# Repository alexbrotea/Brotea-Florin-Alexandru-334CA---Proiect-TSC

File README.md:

## 1. Diagrama bloc

Mai jos este diagrama bloc a sistemului, ilustrand modul in care componentele interactioneaza cu unitatea centrala (MCU):

```mermaid
graph TD
    BATT[Baterie LiPo] -->|V_BATT| CHG[LiPo Charger MCP73831]
    USB[USB-C Connector] -->|5V| CHG
    CHG --> DCDC[DC/DC Converter]
    DCDC -->|3.3V| MCU(nRF52840 MCU)
    
    BATT -->|Monitorizare| FG[Fuel Gauge MAX17048]
    FG <-->|I2C| MCU
    
    MCU <-->|I2C| IMU[Senzor IMU BMI270]
    MCU <-->|I2C| HAP[Haptic Driver DRV2605L]
    
    MCU <-->|SPI| EPD_CON[E-Paper Display Connector]
    MCU -->|Control| EPD_DRV[E-Paper Drive Circuit]
    
    BTN[Butoane SW_UP, SW_ENT, SW_DN] -->|GPIO| MCU
    SWD[SWD Interface] <-->|Debug| MCU
```
## 2. Bill of Materials

| Componenta / Modul | Rol in proiect | Cod piesa JLCPCB |
|-------------------|----------------|------------------|
| nRF52840 | Microcontroler cu Bluetooth LE | C138981 |
| MAX17048G+T10 | Fuel Gauge (monitorizare baterie) | C149814 |
| BMI270 | IMU 6 axe (accelerometru + giroscop) | C2828345 |
| DRV2605L | Driver haptic (LRA/ERM) | C78152 |
| MCP73831T-2ACI/OT | Incarcator LiPo | C14434 |
| TPD4E05U06DQNR | Protectie ESD (USB-C) | C127411 |

## 3. Functionalitate Hardware

InkTime este construit ca un sistem modular eficient energetic:

### Microcontroller (MCU)
- nRF52840 (ARM Cortex-M4F)
- Bluetooth 5 integrat
- Conectivitate directa cu smartphone

### Alimentare si Incarcare
- Incarcare prin USB-C
- Incarcator dedicat LiPo (MCP73831)
- Protectie ESD integrata
- Monitorizare baterie prin MAX17048:
  - Masoara tensiunea
  - Estimeaza procentul bateriei
  - Consum foarte redus

### Afisaj E-Paper
- Conector FPC cu 24 pini
- Circuit dedicat de drive:
  - MOSFET-uri
  - Retea de condensatori
- Genereaza tensiuni pozitive si negative necesare refresh-ului

### Interfata Utilizator
- 3 butoane:
  - SW_UP
  - SW_ENT
  - SW_DN
- Debouncing hardware
- Feedback haptic:
  - Driver DRV2605L
  - Motor vibratii (LRA/ERM)
- IMU pentru detectarea miscarii mainii

## 4. Mapare pini (Pinout nRF52840)
| Periferic       | Semnal                 | Pin MCU                       | Descriere                        |
| --------------- | ---------------------- | ----------------------------- | -------------------------------- |
| I2C Bus         | SDA / SCL              | P0.26 / P0.27                 | Magistrala comuna pentru senzori |
| E-Paper SPI     | SCK / MOSI             | P0.17 / P0.20                 | Transfer rapid de date           |
| E-Paper Control | CS / DC / RST / BUSY   | P0.22 / P0.24 / P0.15 / P0.13 | Control display                  |
| Butoane         | SW_UP / SW_ENT / SW_DN | P0.06 / P0.08 / P0.12         | Input cu intreruperi             |
| Haptic          | EN / IN                | P0.05                         | Activare driver haptic           |
| USB Sense       | VBUS                   | P0.02                         | Detectare cablu USB              |

## 5. Design Log & Review
- Placa pe 2 straturi
- Forma ergonomica adaptata carcasei
- Plan de masa optimizat pentru:
stabilitate RF
performanta Bluetooth
- Grosime minimizata
- Layout compact
- Integrare eficienta

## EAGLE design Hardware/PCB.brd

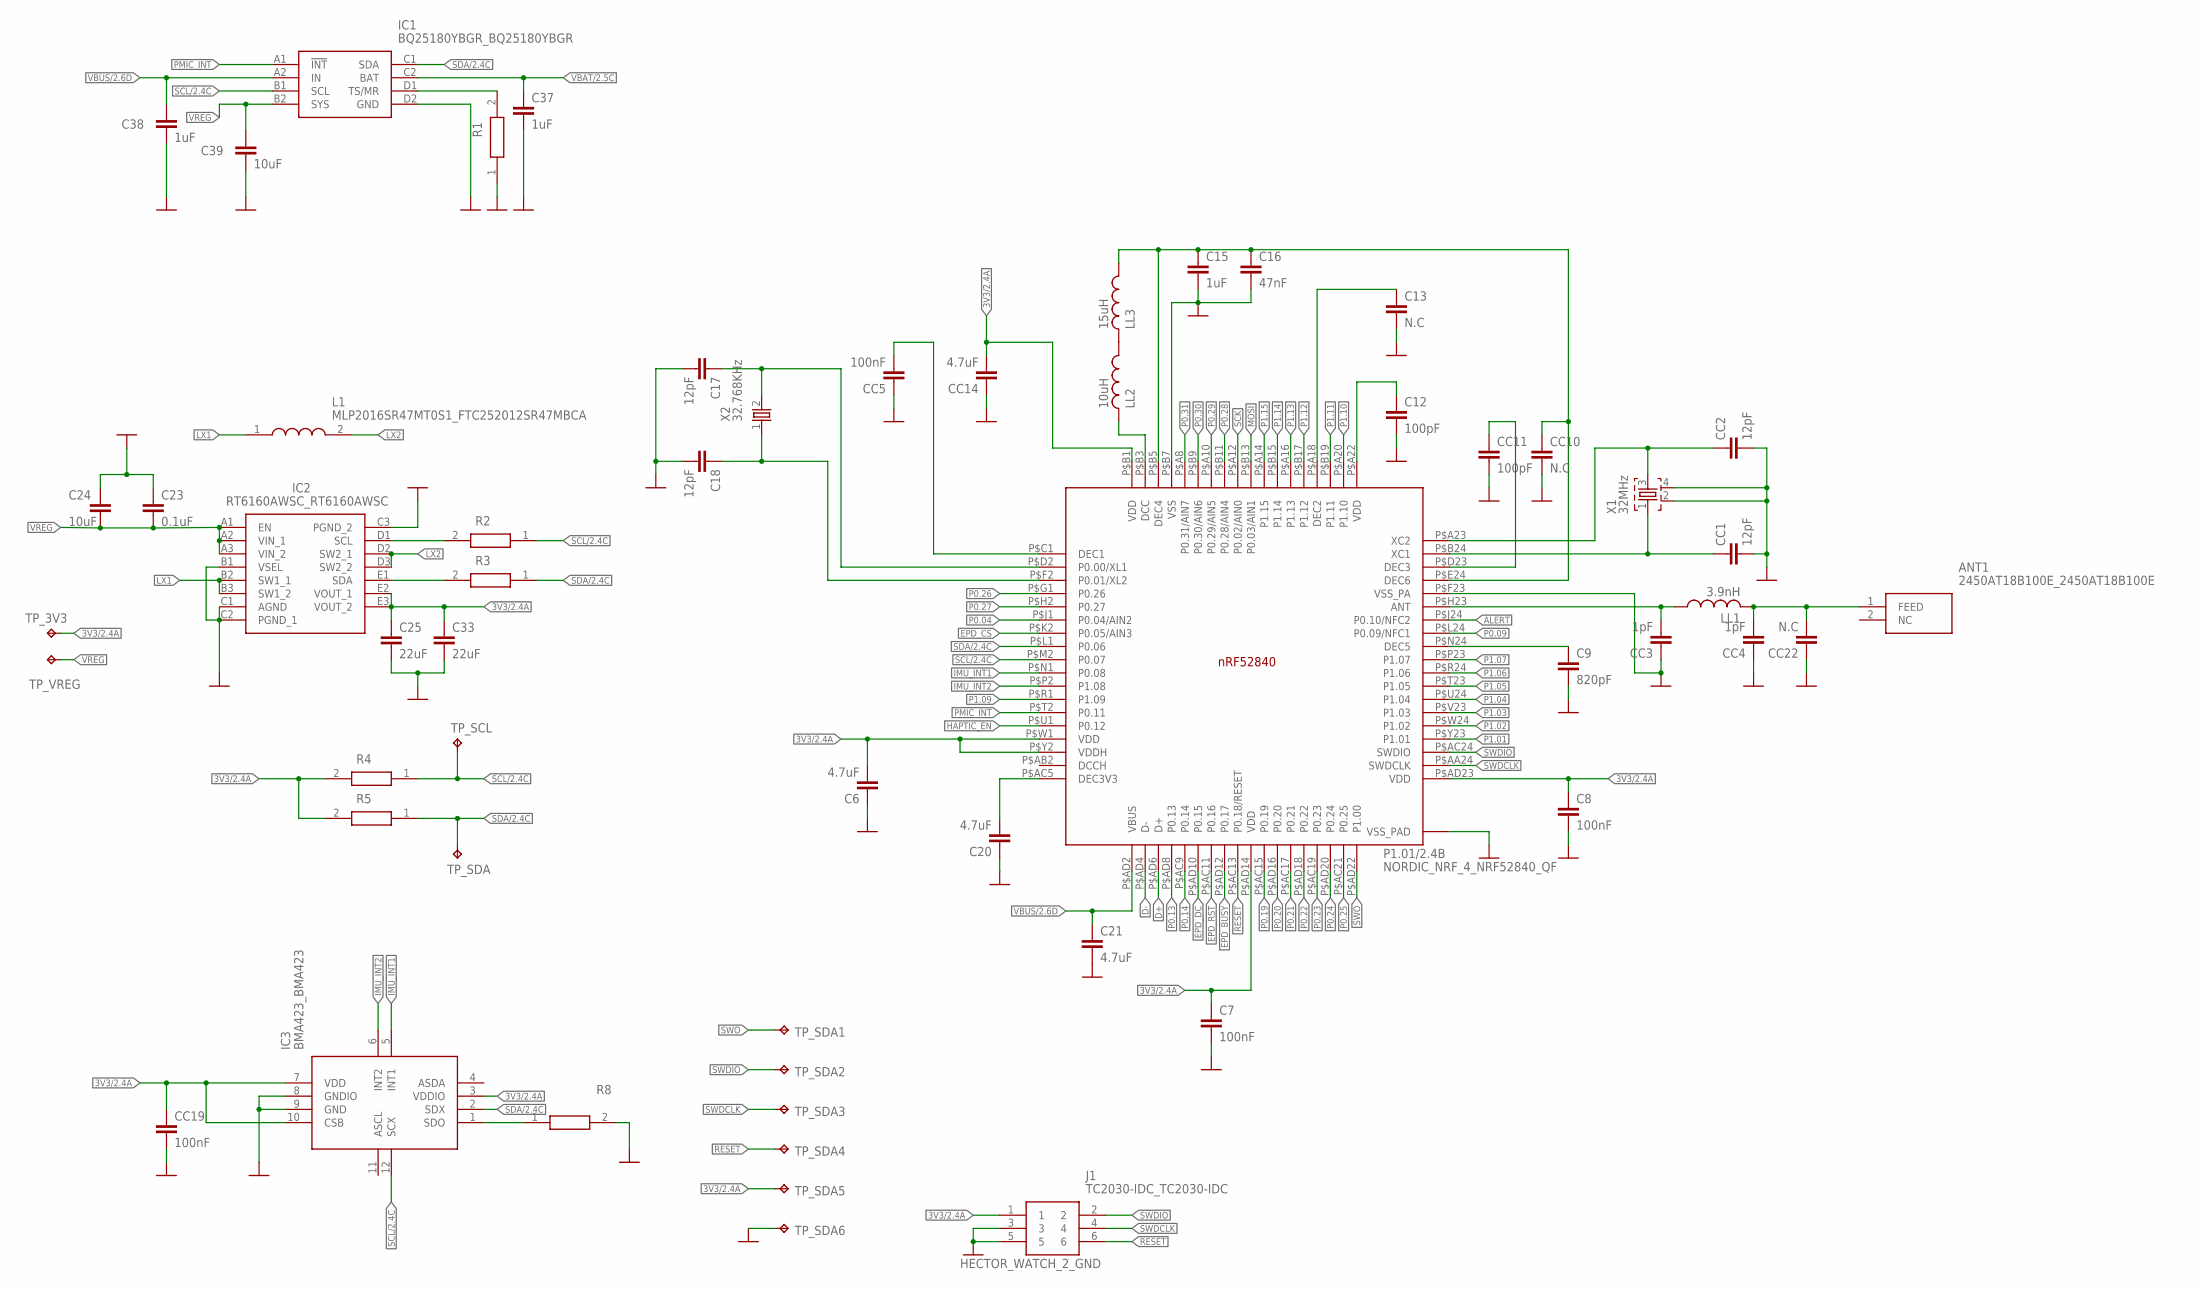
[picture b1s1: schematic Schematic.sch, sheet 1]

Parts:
ANT1: 2450AT18B100E_2450AT18B100E; 2450AT18B100E_ANTC3216X140N
C6, C20, C21: 4.7uF; NORDIC_NRF_3_RESC0402_M
C7, C8: 100nF; NORDIC_NRF_3_RESC0402_M
C9: 820pF; NORDIC_NRF_3_RESC0402_M
C12: 100pF; NORDIC_NRF_3_RESC0402_M
C13: N.C; NORDIC_NRF_3_RESC0402_M
C15, C37, C38: 1uF; NORDIC_NRF_3_RESC0402_M
C16: 47nF; NORDIC_NRF_3_RESC0402_M
C17, C18: 12pF; NORDIC_NRF_3_RESC0402_M
C23: 0.1uF; NORDIC_NRF_3_RESC0402_M
C24, C39: 10uF; NORDIC_NRF_3_RESC0402_M
C25, C33: 22uF; NORDIC_NRF_3_RESC0402_M
CC1, CC2: 12pF; NORDIC_NRF_3_RESC0402_M
CC3, CC4: 1pF; NORDIC_NRF_3_RESC0402_M
CC5, CC19: 100nF; NORDIC_NRF_3_RESC0402_M
CC10, CC22: N.C; NORDIC_NRF_3_RESC0402_M
CC11: 100pF; NORDIC_NRF_3_RESC0402_M
CC14: 4.7uF; NORDIC_NRF_3_RESC0402_M
IC1: BQ25180YBGR_BQ25180YBGR; BQ25180YBGR_BGA8C40P2X4_100X155X50
IC2: RT6160AWSC_RT6160AWSC; RT6160AWSC_BGA15C40P3X5_140X230X60
IC3: BMA423_BMA423
J1: TC2030-IDC_TC2030-IDC; TC2030-IDC_TC2030IDC
L1: MLP2016SR47MT0S1_FTC252012SR47MBCA; MLP2016SR47MT0S1_INDC2016X100N
LL1: 3.9nH; NORDIC_NRF_2_RESC0402_M
LL2: 10uH; NORDIC_NRF_2_RESC0402_M
LL3: 15uH; NORDIC_NRF_2_RESC0402_M
P1.01/2.4B: NORDIC_NRF_4_NRF52840_QF; NORDIC_NRF_4_AQFN50P700X700X85_HS-74N
R1: 10K; CPF0201D7K68C1_0201
R2, R3, R4, R5, R8: CPF0201D7K68C1_CPF0201D7K68C1; CPF0201D7K68C1_0201
TP_3V3: HECTOR_WATCH_1_TPTP20R; HECTOR_WATCH_1_TP20R
TP_SCL: HECTOR_WATCH_1_TPTP20R; HECTOR_WATCH_1_TP20R
TP_SDA, TP_SDA1, TP_SDA2, TP_SDA3, TP_SDA4, TP_SDA5, TP_SDA6: HECTOR_WATCH_1_TPTP20R; HECTOR_WATCH_1_TP20R
TP_VREG: HECTOR_WATCH_1_TPTP20R; HECTOR_WATCH_1_TP20R
X1: 32MHz; NORDIC_NRF_BT-XTAL_2016_N
X2: 32.768KHz; NORDIC_NRF_1_XTAL_3215_N

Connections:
3V3/2.4A: C6.2, C7.1, C8.1, C25.1, C33.1, CC14.2, CC19.1, IC2.E2 (VOUT_1), IC2.E3 (VOUT_2), IC3.3 (VDDIO), IC3.7 (VDD), IC3.10 (CSB), J1.1, P1.01/2.4B.P$AD14 (VDD), P1.01/2.4B.P$AD23 (VDD), P1.01/2.4B.P$B1 (VDD), P1.01/2.4B.P$W1 (VDD), P1.01/2.4B.P$Y2 (VDDH), R4.2, R5.2, TP_3V3.TP, TP_SDA5.TP
ALERT: P1.01/2.4B.P$J24 (P0.10/NFC2); also elsewhere on the board
D+: P1.01/2.4B.P$AD6 (D+); also elsewhere on the board
D-: P1.01/2.4B.P$AD4 (D-); also elsewhere on the board
EPD_BUSY: P1.01/2.4B.P$AD12 (P0.17); also elsewhere on the board
EPD_CS: P1.01/2.4B.P$K2 (P0.05/AIN3); also elsewhere on the board
EPD_DC: P1.01/2.4B.P$AD10 (P0.15); also elsewhere on the board
EPD_RST: P1.01/2.4B.P$AC11 (P0.16); also elsewhere on the board
GND: C6.1, C7.2, C8.2, C9.2, C12.2, C13.2, C15.2, C16.2, C17.2, C18.2, C20.1, C21.2, C23.1, C24.1, C25.2, C33.2, C37.2, C38.2, C39.2, CC1.2, CC2.2, CC3.1, CC4.1, CC5.1, CC10.2, CC11.2, CC14.1, CC19.2, CC22.1, IC1.D2 (GND), IC2.B1 (VSEL), IC2.C1 (AGND), IC2.C2 (PGND_1), IC2.C3 (PGND_2), IC3.8 (GNDIO), IC3.9 (GND), J1.3, J1.5, P1.01/2.4B.P$74 (VSS_PAD), P1.01/2.4B.P$75 (VSS_PAD), P1.01/2.4B.P$76 (VSS_PAD), P1.01/2.4B.P$77 (VSS_PAD), P1.01/2.4B.P$78 (VSS_PAD), P1.01/2.4B.P$79 (VSS_PAD), P1.01/2.4B.P$80 (VSS_PAD), P1.01/2.4B.P$81 (VSS_PAD), P1.01/2.4B.P$82 (VSS_PAD), P1.01/2.4B.P$83 (VSS_PAD), P1.01/2.4B.P$84 (VSS_PAD), P1.01/2.4B.P$85 (VSS_PAD), P1.01/2.4B.P$86 (VSS_PAD), P1.01/2.4B.P$87 (VSS_PAD), P1.01/2.4B.P$88 (VSS_PAD), P1.01/2.4B.P$89 (VSS_PAD), P1.01/2.4B.P$90 (VSS_PAD), P1.01/2.4B.P$B7 (VSS), P1.01/2.4B.P$F23 (VSS_PA), R1.1, R8.2, TP_SDA6.TP, X1.2, X1.4; also elsewhere on the board
HAPTIC_EN: P1.01/2.4B.P$U1 (P0.12); also elsewhere on the board
IMU_INT1: IC3.5 (INT1), P1.01/2.4B.P$N1 (P0.08)
IMU_INT2: IC3.6 (INT2), P1.01/2.4B.P$P2 (P1.08)
LX1: IC2.B2 (SW1_1), IC2.B3 (SW1_2), L1.1
LX2: IC2.D2 (SW2_1), IC2.D3 (SW2_2), L1.2
MOSI: P1.01/2.4B.P$B13 (P0.03/AIN1); also elsewhere on the board
unnamed: IC1.D1 (TS/MR), R1.2
unnamed: C9.1, P1.01/2.4B.P$N24 (DEC5)
unnamed: CC3.2, LL1.1, P1.01/2.4B.P$H23 (ANT)
unnamed: IC2.D1 (SCL), R2.2
unnamed: IC2.E1 (SDA), R3.2
unnamed: C20.2, P1.01/2.4B.P$AC5 (DEC3V3)
unnamed: ANT1.1 (FEED), CC4.2, CC22.2, LL1.2
unnamed: CC1.1, P1.01/2.4B.P$B24 (XC1), X1.1
unnamed: CC2.1, P1.01/2.4B.P$A23 (XC2), X1.3
unnamed: CC11.1, P1.01/2.4B.P$D23 (DEC3)
unnamed: C18.1, P1.01/2.4B.P$F2 (P0.01/XL2), X2.1
unnamed: C12.1, P1.01/2.4B.P$A22 (VDD)
unnamed: C13.1, P1.01/2.4B.P$A18 (DEC2)
unnamed: LL2.1, LL3.2
unnamed: LL2.2, P1.01/2.4B.P$B3 (DCC)
unnamed: C15.1, C16.1, CC10.1, LL3.1, P1.01/2.4B.P$B5 (DEC4), P1.01/2.4B.P$E24 (DEC6)
unnamed: C17.1, P1.01/2.4B.P$D2 (P0.00/XL1), X2.2
unnamed: IC3.1 (SDO), R8.1
unnamed: CC5.2, P1.01/2.4B.P$C1 (DEC1)
P0.04: P1.01/2.4B.P$J1 (P0.04/AIN2)
P0.09: P1.01/2.4B.P$L24 (P0.09/NFC1)
P0.13: P1.01/2.4B.P$AD8 (P0.13); also elsewhere on the board
P0.14: P1.01/2.4B.P$AC9 (P0.14); also elsewhere on the board
P0.19: P1.01/2.4B.P$AC15 (P0.19)
P0.20: P1.01/2.4B.P$AD16 (P0.20)
P0.21: P1.01/2.4B.P$AC17 (P0.21)
P0.22: P1.01/2.4B.P$AD18 (P0.22)
P0.23: P1.01/2.4B.P$AC19 (P0.23)
P0.24: P1.01/2.4B.P$AD20 (P0.24)
P0.25: P1.01/2.4B.P$AC21 (P0.25)
P0.26: P1.01/2.4B.P$G1 (P0.26)
P0.27: P1.01/2.4B.P$H2 (P0.27)
P0.28: P1.01/2.4B.P$B11 (P0.28/AIN4)
P0.29: P1.01/2.4B.P$A10 (P0.29/AIN5)
P0.30: P1.01/2.4B.P$B9 (P0.30/AIN6)
P0.31: P1.01/2.4B.P$A8 (P0.31/AIN7)
P1.01: P1.01/2.4B.P$Y23 (P1.01); also elsewhere on the board
P1.02: P1.01/2.4B.P$W24 (P1.02); also elsewhere on the board
P1.03: P1.01/2.4B.P$V23 (P1.03)
P1.04: P1.01/2.4B.P$U24 (P1.04)
P1.05: P1.01/2.4B.P$T23 (P1.05)
P1.06: P1.01/2.4B.P$R24 (P1.06)
P1.07: P1.01/2.4B.P$P23 (P1.07)
P1.09: P1.01/2.4B.P$R1 (P1.09)
P1.10: P1.01/2.4B.P$A20 (P1.10)
P1.11: P1.01/2.4B.P$B19 (P1.11)
P1.12: P1.01/2.4B.P$B17 (P1.12)
P1.13: P1.01/2.4B.P$A16 (P1.13)
P1.14: P1.01/2.4B.P$B15 (P1.14)
P1.15: P1.01/2.4B.P$A14 (P1.15)
PMIC_INT: IC1.A1 (!INT), P1.01/2.4B.P$T2 (P0.11)
RESET: J1.6, P1.01/2.4B.P$AC13 (P0.18/RESET), TP_SDA4.TP
SCK: P1.01/2.4B.P$A12 (P0.02/AIN0); also elsewhere on the board
SCL/2.4C: IC1.B1 (SCL), IC3.12 (SCX), P1.01/2.4B.P$M2 (P0.07), R2.1, R4.1, TP_SCL.TP
SDA/2.4C: IC1.C1 (SDA), IC3.2 (SDX), P1.01/2.4B.P$L1 (P0.06), R3.1, R5.1, TP_SDA.TP
SWDCLK: J1.4, P1.01/2.4B.P$AA24 (SWDCLK), TP_SDA3.TP
SWDIO: J1.2, P1.01/2.4B.P$AC24 (SWDIO), TP_SDA2.TP
SWO: P1.01/2.4B.P$AD22 (P1.00), TP_SDA1.TP
VBAT/2.5C: C37.1, IC1.C2 (BAT)
VBUS/2.6D: C21.1, C38.1, IC1.A2 (IN), P1.01/2.4B.P$AD2 (VBUS)
VREG: C23.2, C24.2, C39.1, IC1.B2 (SYS), IC2.A1 (EN), IC2.A2 (VIN_1), IC2.A3 (VIN_2), TP_VREG.TP

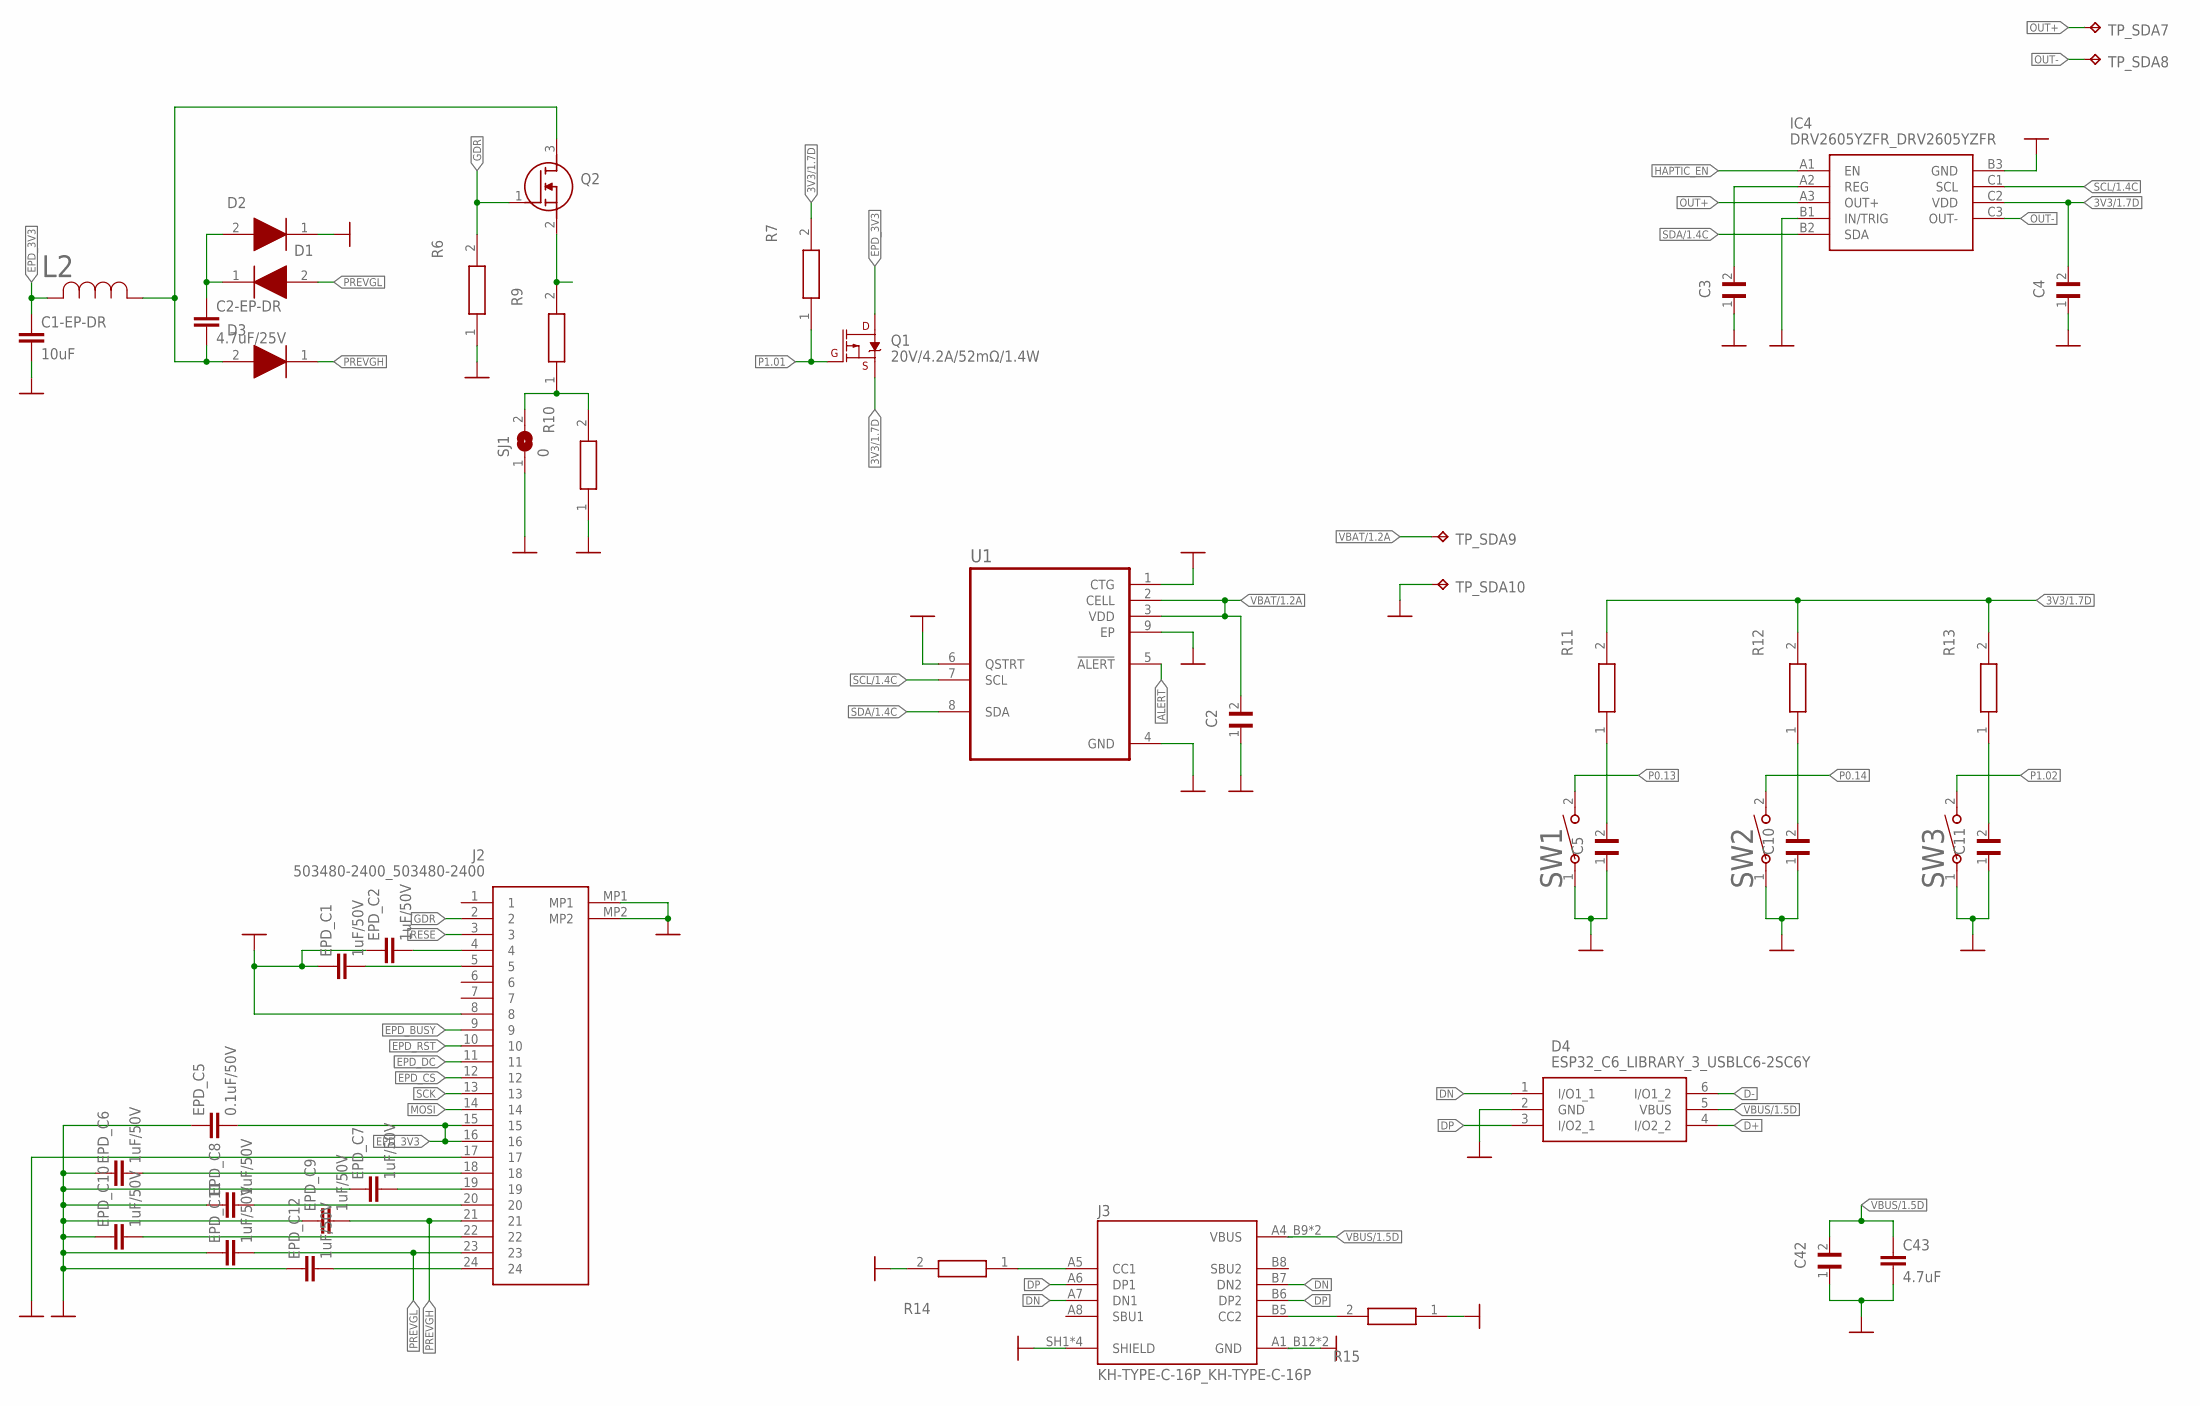
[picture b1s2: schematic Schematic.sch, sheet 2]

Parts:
C1-EP-DR: 10uF; NORDIC_NRF_3_RESC0402_M
C2, C5, C10, C11, C42: GRM011R60J152KE01L_1_GRM011R60J152KE01L; GRM011R60J152KE01L_1_0201
C2-EP-DR: 4.7uF/25V; ESP32_C6_LIBRARY_1_ESP32_WROVER_EAGLE-LTSPICE_C0402
C3: 1uF; GRM011R60J152KE01L_1_0201
C4: 0.1uF; GRM011R60J152KE01L_1_0201
C43: 4.7uF; NORDIC_NRF_3_RESC0402_M
D1, D2, D3: ESP32_C6_LIBRARY_5_MBR0530; ESP32_C6_LIBRARY_5_SOD3716X135N
D4: ESP32_C6_LIBRARY_3_USBLC6-2SC6Y; ESP32_C6_LIBRARY_3_SOT95P280X145-6N
EPD_C1, EPD_C2, EPD_C6, EPD_C7, EPD_C8, EPD_C9, EPD_C10, EPD_C11, EPD_C12: 1uF/50V; NORDIC_NRF_3_RESC0402_M
EPD_C5: 0.1uF/50V; NORDIC_NRF_3_RESC0402_M
IC4: DRV2605YZFR_DRV2605YZFR; DRV2605YZFR_BGA9C50P3X3_144X144X62
J2: 503480-2400_503480-2400; 503480-2400_5034802400
J3: KH-TYPE-C-16P_KH-TYPE-C-16P; KH-TYPE-C-16P_KINGHELM_KH-TYPE-C-16P
L2: ESP32_C6_LIBRARY_2_744043680IND_4828-WE-TPC_WRE; ESP32_C6_LIBRARY_2_IND_4828-WE-TPC_WRE
Q1: 20V/4.2A/52mΩ/1.4W; ESP32_C6_LIBRARY_4_ESP32_C6_LIBRARY_4_ESP32_C6_LIBRARY_4_ES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
Q2: ESP32_C6_LIBRARY_6_SI1308EDL-T1-GE3; ESP32_C6_LIBRARY_6_SOT65P210X110-3N
R6, R7, R9, R10, R11, R12, R13, R14, R15: CPF0201D7K68C1_CPF0201D7K68C1; CPF0201D7K68C1_0201
SJ1: 0; ESP32_C6_LIBRARY_7_JUMPER_SJ
SW1, SW2, SW3: 2025-10-22_07-23-44_LIBRARY_EVP-AKE31ASW_EVP-AKE3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; 2025-10-22_07-23-44_LIBRARY_SW_EVP-AKE31A_PAN
TP_SDA7, TP_SDA8, TP_SDA9, TP_SDA10: HECTOR_WATCH_1_TPTP20R; HECTOR_WATCH_1_TP20R
U1: ESP32_C6_LIBRARY_MAX17048G+T10; ESP32_C6_LIBRARY_SON50P200X200X80-9N

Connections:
3V3/1.7D: C4.2, IC4.C2 (VDD), Q1.2 (S), R7.2, R11.2, R12.2, R13.2
ALERT: U1.5 (!ALERT); also elsewhere on the board
D+: D4.4 (I/O2_2); also elsewhere on the board
D-: D4.6 (I/O1_2); also elsewhere on the board
DN: D4.1 (I/O1_1), J3.A7 (DN1), J3.B7 (DN2)
DP: D4.3 (I/O2_1), J3.A6 (DP1), J3.B6 (DP2)
EPD_3V3: C1-EP-DR.1, EPD_C5.2, J2.15, J2.16, L2.2, Q1.3 (D)
EPD_BUSY: J2.9; also elsewhere on the board
EPD_CS: J2.12; also elsewhere on the board
EPD_DC: J2.11; also elsewhere on the board
EPD_RST: J2.10; also elsewhere on the board
GDR: J2.2, Q2.1 (G), R6.2
GND: C1-EP-DR.2, C2.1, C3.1, C4.1, C5.1, C10.1, C11.1, C42.1, C43.2, D2.1 (K), D4.2 (GND), EPD_C1.1, EPD_C2.1, EPD_C5.1, EPD_C6.1, EPD_C7.1, EPD_C8.1, EPD_C9.1, EPD_C10.1, EPD_C11.1, EPD_C12.1, IC4.B1 (IN/TRIG), IC4.B3 (GND), J2.8, J2.17, J2.MP1, J2.MP2, J3.A1_B12 (GND), J3.A12_B1 (GND), J3.SH1 (SHIELD), J3.SH2 (SHIELD), J3.SH3 (SHIELD), J3.SH4 (SHIELD), R6.1, R10.1, R14.2, R15.1, SJ1.1, SW1.1, SW2.1, SW3.1, TP_SDA10.TP, U1.1 (CTG), U1.4 (GND), U1.6 (QSTRT), U1.9 (EP); also elsewhere on the board
HAPTIC_EN: IC4.A1 (EN); also elsewhere on the board
MOSI: J2.14; also elsewhere on the board
unnamed: C2-EP-DR.1, D1.1 (K), D2.2 (A)
unnamed: Q2.2 (S), R9.2
unnamed: R9.1, R10.2, SJ1.2
unnamed: C2-EP-DR.2, D3.2 (A), L2.1, Q2.3 (D)
unnamed: EPD_C2.2, J2.4
unnamed: EPD_C1.2, J2.5
unnamed: J3.B5 (CC2), R15.2
unnamed: EPD_C7.2, J2.19
unnamed: C5.2, R11.1
unnamed: EPD_C12.2, J2.24
unnamed: EPD_C6.2, J2.18
unnamed: EPD_C8.2, J2.20
unnamed: C10.2, R12.1
unnamed: EPD_C10.2, J2.22
unnamed: C11.2, R13.1
unnamed: J3.A5 (CC1), R14.1
unnamed: C3.2, IC4.A2 (REG)
OUT+: IC4.A3 (OUT+), TP_SDA7.TP
OUT-: IC4.C3 (OUT-), TP_SDA8.TP
P0.13: SW1.2; also elsewhere on the board
P0.14: SW2.2; also elsewhere on the board
P1.01: Q1.1 (G), R7.1; also elsewhere on the board
P1.02: SW3.2; also elsewhere on the board
PREVGH: D3.1 (K), EPD_C9.2, J2.21
PREVGL: D1.2 (A), EPD_C11.2, J2.23
RESE: J2.3
SCK: J2.13; also elsewhere on the board
SCL/1.4C: IC4.C1 (SCL), U1.7 (SCL)
SDA/1.4C: IC4.B2 (SDA), U1.8 (SDA)
VBAT/1.2A: C2.2, TP_SDA9.TP, U1.2 (CELL), U1.3 (VDD)
VBUS/1.5D: C42.2, C43.1, D4.5 (VBUS), J3.A4_B9 (VBUS), J3.A9_B4 (VBUS)

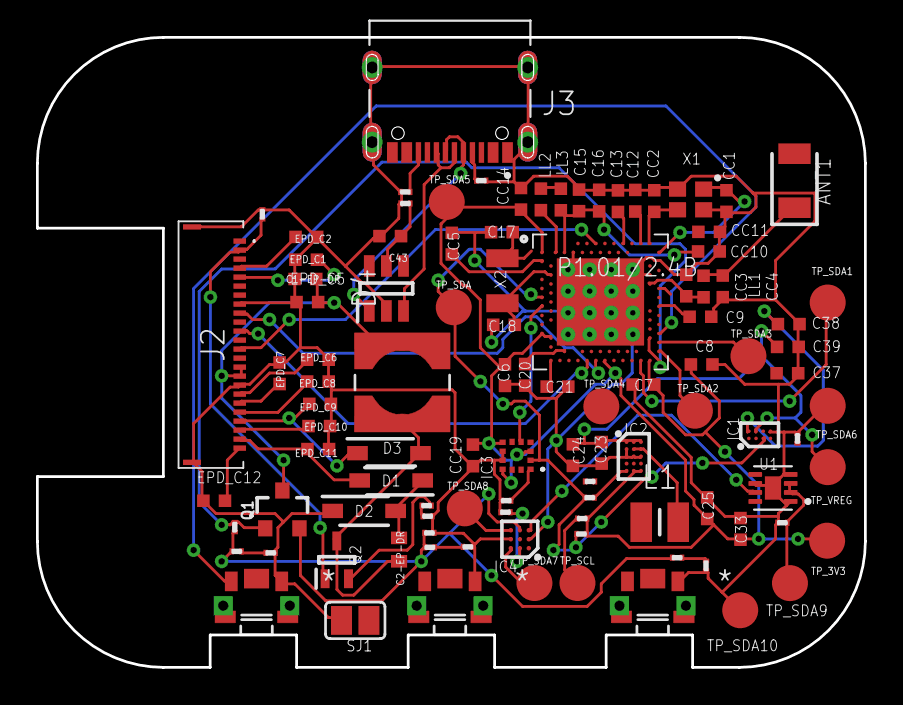
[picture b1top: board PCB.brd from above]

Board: 2 copper layers, 46.0 x 35.0 mm, 103 parts (0 on the bottom side), 79 nets.

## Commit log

2026-04-10 first deadline
2026-04-19 project done

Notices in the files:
parts and their libraries:
COPYRIGHT: Copyright (C) 2024 Ultra Librarian. All rights reserved.
COPYRIGHT: Copyright (C) 2025 Ultra Librarian. All rights reserved.
